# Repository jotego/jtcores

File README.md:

# JTCORES FPGA Arcade Hardware by Jose Tejada (@topapate)

You can show your appreciation through
* [Patreon](https://patreon.com/jotego)
* [Paypal](https://paypal.me/topapate)
* [Github](https://github.com/sponsors/jotego)

Yes, you always wanted to have an arcade board at home. First you couldn't get it because your parents somehow did not understand you. Then you grow up and your wife doesn't understand you either. Don't worry, JT cores are here to the rescue.

I hope you will have as much fun with this project as I had while working on it!

## Wanna play?

You can find the list of supported games in [jtbin/game_list](https://github.com/jotego/jtbin/blob/master/game_list.md). That list is actually an output of the source code of this repository and gets updated every release. There are 1250+ supported titles at the moment ( September 2026 ).

The compiled versions for some FPGA platforms are in [JTBIN](https://github.com/jotego/jtbin). Most cores are released early for [patrons](https://patreon.com/jotego) so check it out too. [JTFRAME](modules/jtframe/README.md) supports more FPGA platforms than the ones publised in JTBIN. You are welcome to compile the cores for the other platforms. Distribution of the core binary files together with copyrighted ROM files is not permitted.

# Compilation - JTFRAME

Refer to [JTFRAME](modules/jtframe/README.md) for compilation instructions and general information about how the cores are organized.

## Private Support Files

Set the `JOTEGO` environment variable to the directory used for private JTCORES support files, including core-regression and scene-regression data used by privately run GitHub Actions. Scene data is stored below `$JOTEGO/scenes/<core-name>/<set-name>`.

When `jtsim -s <scene>` is run from a core verification folder such as `cores/rastan/ver/rbisland`, it requires `JOTEGO` and creates `scenes` as a symbolic link to `$JOTEGO/scenes/rastan/rbisland`. Define `JOTEGO` before running scene simulations.

Master branch health:

# Schematics

Some core have KiCAD schematics for the arcade PCB. This is part of the core research effort and it is important on its own. The schematics folders are called *sch* and can be found in some core folders.

All schematics use the same set of symbol components from [JTKICAD](modules/jtkicad/README.md)

## Troubleshooting

* If you have in-game problems, please read the text file specific to that core. Sometimes it's just that the games has more buttons than you think
* Continue the game: some early arcade games require you to hold the fire button while pressing 1P to continue

## Keyboard

For MiST and MiSTer: games can be controlled with both game pads and keyboard. The keyboard follows the same layout as MAME's default.

    F2      Service mode
    F3      Game reset
    T       Tilt
    P       Pause (in some games, you can disable the credits screen by pressing 1P)
    1,2,3,4 1P..4O start buttons
    5,6     Left and right coin inputs
    9       Service

    cursors 1P direction
    CTRL    1P button 1
    ALT     1P button 2
    space   1P button 3

    R,F,G,D 2P direction
    Q,S,A   2P buttons 3,2 and 1

# Credits

Jose Tejada Gomez. Twitter @topapate
The project is hosted in http://www.github.com/jotego/jtcores
License: GPL3, you are obligued to publish your code if you use mine

Thank you all!
```
+--------------------------------------------------------------------------------+
|oooooooooooooooooooooooooooooooooo+++++++++++ooooooooooooooooooooooooooooooooooo|
|ooooooooooooooooooooooooooooooooo+. .    . .+ooooooooooooooooooooooooooooooooooo|
|ooooooooooooooooooooooooooooooooo~         :o++ooooooooooooooooooooooooooooooooo|
|oooooooooooooooooooooooooooo+ooo+.        .++.:oo+oo+oooooo+o+oo+oooooo++ooooooo|
|ooooooooooooooooooooooooo+.......          .. .............................:oooo|
|oooooooooooooooooooooooo+.                                                .+o+oo|
|oooooooooooooooooooooooo:                                                 :o:.+o|
|ooooooooooooooooooooooo+.                                                .++.:oo|
|ooooooooooooooooooooooo:.....           ...........          ....... ....:o~.+oo|
|oooooooooooooooooooooooo+++++~         ~+++:++:++++.         ++++++++++++++.+ooo|
|oooooooooooooooooooooooooo+:~         .++.~:::::::.         .o+.~:::::::::::+ooo|
|oooooooooooooooooooooooooooo:         :o~.+oooooo+.         ++.~oooooooooooooooo|
|ooo~........~oooooooooooooo+.        .++.:ooooooo+         ~o:.+oooooooooooooooo|
|oo:         ~o++ooooooooooo.         +o~.ooooooo+.        .++.~ooooooooooooooooo|
|oo.         :+.:ooooooooo+.         ~o+.+ooooooo:         ~o:.+ooooooooooooooooo|
|oo.         ...~:::::::..          .++.~ooooooo+.        .o+.:oooooooooooooooooo|
|oo~                               ~o+..+ooooooo~         +o~.+oooooooooooooooooo|
|oo+.                           .~+o+..+ooooooo+.        .o+.+ooooooooooooooooooo|
|oooo~.                       .:+o+..:+oooooooo.         +o..oooooooooooooooooooo|
|ooooo+:...              ..~:+++:..:+ooooooooo+         .o+.+oooooooooooooooooooo|
|ooooooo+++::::::::::++++++++~~.~++ooooooooooo+:+:::::+:++.~ooooooooooooooooooooo|
|ooooooooo+++:::::::::~:~~~~:++oooooooooooooooooo+::::~::~.+ooooooooooooooooooooo|
|oooooooooooooo+o+oo++++o+ooooooooooooooooooooooo+o+++o++o+oooooooooooooooooooooo|
+--------------------------------------------------------------------------------+
```

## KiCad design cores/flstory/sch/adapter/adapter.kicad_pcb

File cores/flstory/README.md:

# JTFLSTORY, FPGA hardware compatible with Taito's FairyLand Story software

This work is based on the schematic work we did on an original FairyLand arcade
PCB. The board turned out to be full of surprises.

# Differences with Emulation (as of Dec. 2025)

The following features are present on the hardware and seem to be missing on
emulators:

- sprite count limited to 8 per line without blinking, more than 8 sprites can be shown but some will blink
- there is a RAM that sets the scroll-sprite priority, not fixed values
- background tile flip control bits can be ignored by means of a global control bit
- some MCU features are missing, such CPU bus sharing via bus request/acknowledgement
- there are a lot of analog audio features that the sound CPU can control, such as balance, trebble, bass...
  the balance feature of amplifier TA7630 is used to alter the relative volume of the two MSM5232 audio channels, so it plays an important role in how the melody sounds
- there are two palette banks (not one)
- there are two background tile banks (not one)
- the priority bits for sprites and scroll tiles are three and two (fewer used in emulation)
- there is support for a light gun on the board

## PSX GunCon on MiSTer

Light-gun games can use an NTSC PlayStation GunCon through a MiSTer PSX SNAC
adapter. In the OSD select **User port -> PSX GunCon SNAC**. This takes over
the physical User Port, so DB15 joystick and UART modes cannot be used at the
same time; USB/Bluetooth gamepads and keyboard controls still work. Trigger is
action button 1, B/Cross is action button 2, A/Start is Start, and Select is
Coin.

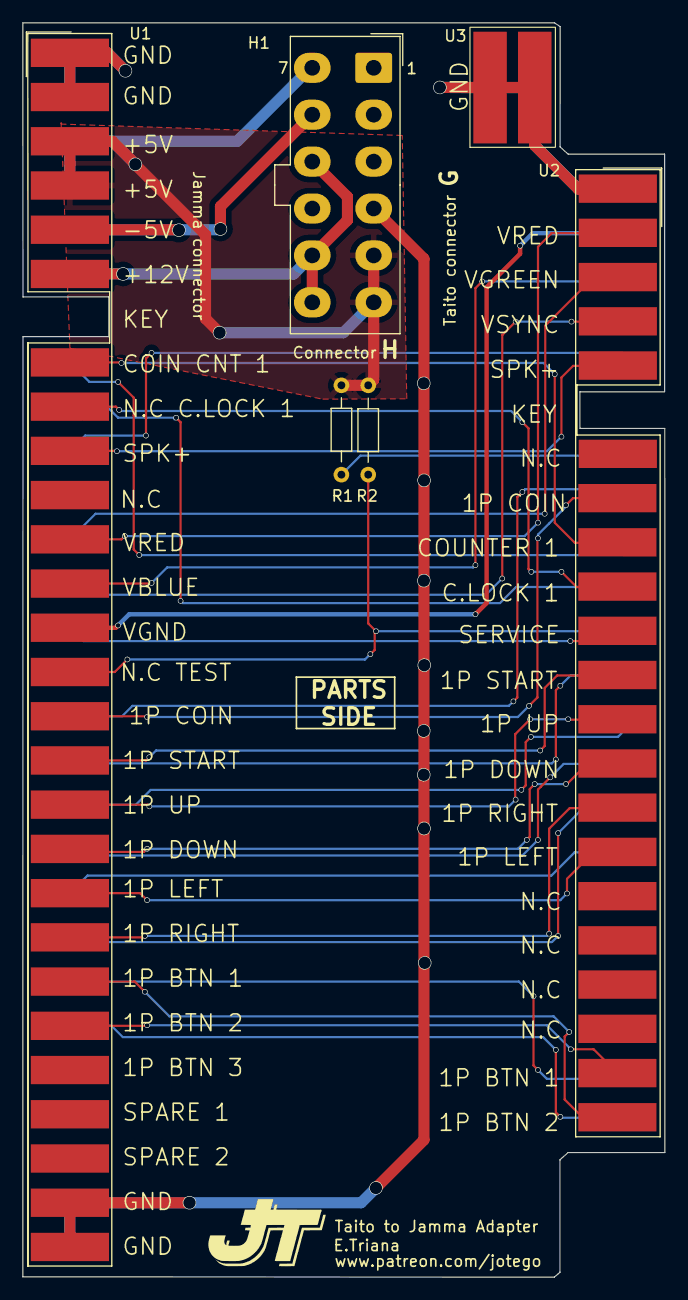
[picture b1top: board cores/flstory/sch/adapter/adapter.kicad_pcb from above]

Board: 2 copper layers, 57.5 x 112.3 mm, 6 parts (0 on the bottom side), 34 nets.

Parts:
H1: Conn_02x06_TB; Molex_Mini-Fit_Jr_5566-12A_2x06_P4.20mm_Vertical
R1, R2: 100kΩ; Resistor P_8mm
U1: JAMMA_MALE; JAMMA MALE
U2: Taito conn_G_adapter_ps; TAITO CONN FOR ADAPTER
U3: Test_point; Test point 3mmx10mm

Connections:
+12V: H1.9, H1.11, H1.12, U1.6 (+12V), U1.F (+12V)
-5V: H1.8, U1.5 (-5V), U1.E (-5V)
/1P_BTN_1: U1.23 (1P_BTN_2), U2.21 (1P_BTN_1)
/1P_BTN_2: U1.22 (1P_BTN_1), U2.22 (1P_BTN_2)
/1P_DOWN: U1.19 (1P_DOWN), U2.14 (1P_DOWN)
/1P_LEFT: U1.20 (1P_LEFT), U2.16 (1P_LEFT)
/1P_RIGHT: U1.21 (1P_RIGHT), U2.15 (1P_RIGHT)
/1P_START: U1.17 (1P_START), U2.12 (1P_START)
/1P_UP: U1.18 (1P_UP), U2.13 (1P_UP)
/C.LOCK_1: U1.9 (NC_C.LOCK_1), U2.10 (C.LOCK_1)
/COIN_1: U1.16 (COIN_1), U2.8 (COIN_1)
/COUNTER_1: U1.8 (COIN_CNT_1), U2.9 (COUNTER_1)
/SERVICE: U1.R (SERVICE), U2.11 (SERVICE)
/SPEAKER(+): U1.10 (SPEAKER_(+)), U2.5 (SPEACKER(+))
/TILT: R2.1, U1.15 (TILT), U2.M (TILT)
/VBLUE: U1.13 (VBLUE), U2.C (VBLUE)
/VGND: U1.14 (VIDEO_GND), U2.B (VIDEO_GND)
/VGREEN: U1.N (VGREEN), U2.3 (VGREEN)
/VRED: U1.12 (VRED), U2.2 (VRED)
/VSYNC: U1.P (VSYNC), U2.4 (VSYNC)
GND: H1.1, H1.2, H1.3, H1.4, U1.1 (GND), U1.2 (GND), U1.27 (GND), U1.28 (GND), U1.A (GND), U1.B (GND), U1.e (GND), U1.f (GND), U2.1 (GND), U2.A (GND), U3.1, U3.2, U3.3, U3.4
unnamed: U1.Z (2P_BTN_1), U2.Y (2P_BTN_1)
unnamed: U1.a (2P_BTN_2), U2.Z (2P_BTN_2)
unnamed: U1.W (2P_DOWN), U2.R (2P_DOWN)
unnamed: U1.X (2P_LEFT), U2.T (2P_LEFT)
unnamed: U1.Y (2P_RIGHT), U2.S (2P_RIGHT)
unnamed: U1.U (2P_START), U2.N (2P_START)
unnamed: U1.V (2P_UP), U2.P (2P_UP)
unnamed: U1.T (COIN_2), U2.J (COIN_2)
unnamed: U1.J (COIN_CNT_2), U2.K (COUNTER_2)
unnamed: U1.K (NC_C.LOCK_2), U2.L (C.LOCK_2)
unnamed: U1.L (SPEAKER_(-)), U2.E (SPEAKER(-))
unnamed: R1.2, U2.H (RESET)
VCC: H1.5, H1.6, H1.7, R1.1, R2.2, U1.3 (+5V), U1.4 (+5V), U1.C (+5V), U1.D (+5V)

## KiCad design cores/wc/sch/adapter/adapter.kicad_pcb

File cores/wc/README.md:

# Grid Iron

# Test Mode

- Hold 1P and 2P while resetting the machine to enter test mode
- Hold shot button to keep the grid on display. Press again to continue

# Simulation Notes

| Simulation              | Command                   |
|:------------------------|:--------------------------|
| Grid image              | `jtsim -w 270 -video 296` |
| Start of subsidiary CPU | `jtsim -w -video 30`      |

# PCB Notes

The schematic extraction was done from a bootleg board, but it was carefully compared with an original one. These are the differences:

- original PCB has through-hole vias whereas the bootleg has filled vias
- original uses three custom packages from Mitsubishi with logic inside. These were replaced by a small daughter board on the bootleg, serving the same functionality
- different edge connectors
- debug edge connector on video board not present on bootleg
- cabinet input logic partly missing and rewired on the bootleg to replace the trackball interface for a joystick one
- different power amplifier for sound without heat sink on the bootleg
- slightly different frequencies for crystal oscillators (cost reduction?)
- device reference markers (silkscreen) on bootleg have reversed order on bootleg

Note that the schematic passes KiCAD electrical rule check with zero errors.

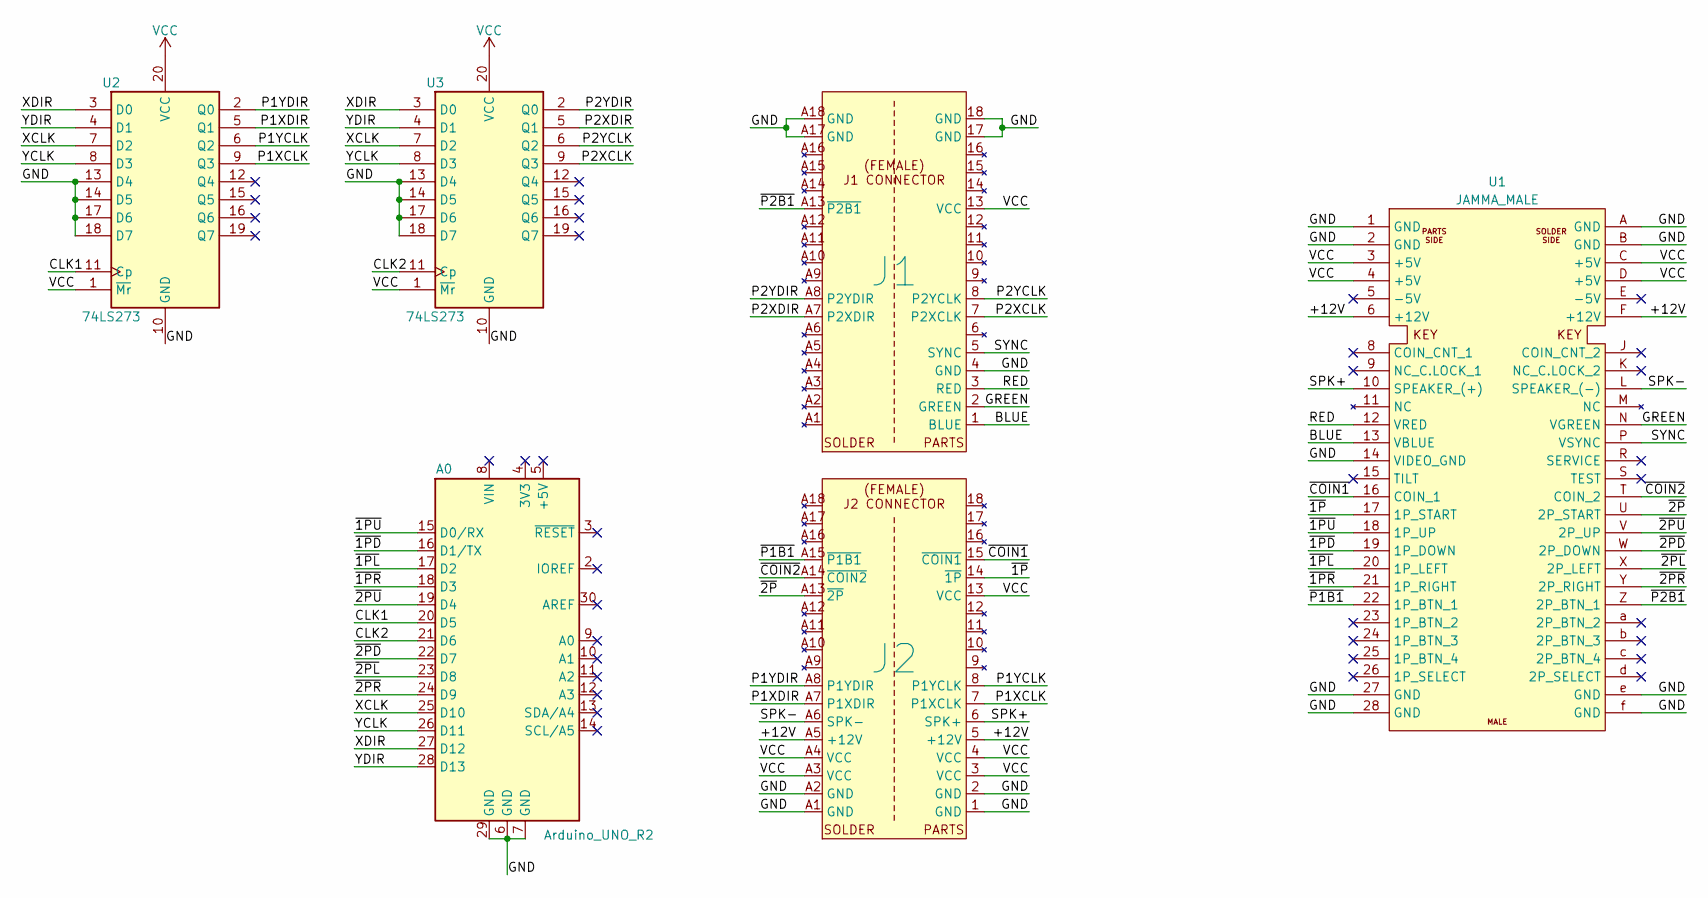
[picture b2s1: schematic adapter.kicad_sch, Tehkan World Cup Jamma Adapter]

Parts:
A0: Arduino_UNO_R2
J1, J2: thekan_wc
U1: JAMMA_MALE; JAMMA MALE
U2, U3: 74LS273; DIP-20_W7.62mm_Socket

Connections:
/+12V: J2.5 (+12V), J2.A5 (+12V), U1.6 (+12V), U1.F (+12V)
/BLUE: J1.1 (BLUE), U1.13 (VBLUE)
/CLK1: A0.20 (D5), U2.11 (Cp)
/CLK2: A0.21 (D6), U3.11 (Cp)
/GND: A0.6 (GND), A0.7 (GND), A0.29 (GND), J1.4 (GND), J1.17 (GND), J1.18 (GND), J1.A17 (GND), J1.A18 (GND), J2.1 (GND), J2.2 (GND), J2.A1 (GND), J2.A2 (GND), U1.1 (GND), U1.2 (GND), U1.14 (VIDEO_GND), U1.27 (GND), U1.28 (GND), U1.A (GND), U1.B (GND), U1.e (GND), U1.f (GND), U2.10 (GND), U2.13 (D4), U2.14 (D5), U2.17 (D6), U2.18 (D7), U3.10 (GND), U3.13 (D4), U3.14 (D5), U3.17 (D6), U3.18 (D7)
/GREEN: J1.2 (GREEN), U1.N (VGREEN)
/P1XCLK: J2.7 (P1XCLK), U2.9 (Q3)
/P1XDIR: J2.A7 (P1XDIR), U2.5 (Q1)
/P1YCLK: J2.8 (P1YCLK), U2.6 (Q2)
/P1YDIR: J2.A8 (P1YDIR), U2.2 (Q0)
/P2XCLK: J1.7 (P2XCLK), U3.9 (Q3)
/P2XDIR: J1.A7 (P2XDIR), U3.5 (Q1)
/P2YCLK: J1.8 (P2YCLK), U3.6 (Q2)
/P2YDIR: J1.A8 (P2YDIR), U3.2 (Q0)
/RED: J1.3 (RED), U1.12 (VRED)
/SPK+: J2.6 (SPK+), U1.10 (SPEAKER_(+))
/SPK-: J2.A6 (SPK-), U1.L (SPEAKER_(-))
/SYNC: J1.5 (SYNC), U1.P (VSYNC)
/XCLK: A0.25 (D10), U2.7 (D2), U3.7 (D2)
/XDIR: A0.27 (D12), U2.3 (D0), U3.3 (D0)
/YCLK: A0.26 (D11), U2.8 (D3), U3.8 (D3)
/YDIR: A0.28 (D13), U2.4 (D1), U3.4 (D1)
/~1PD: A0.16 (D1/TX), U1.19 (1P_DOWN)
/~1PL: A0.17 (D2), U1.20 (1P_LEFT)
/~1PR: A0.18 (D3), U1.21 (1P_RIGHT)
/~1PU: A0.15 (D0/RX), U1.18 (1P_UP)
/~1P: J2.14 (~1P), U1.17 (1P_START)
/~2PD: A0.22 (D7), U1.W (2P_DOWN)
/~2PL: A0.23 (D8), U1.X (2P_LEFT)
/~2PR: A0.24 (D9), U1.Y (2P_RIGHT)
/~2PU: A0.19 (D4), U1.V (2P_UP)
/~2P: J2.A13 (~2P), U1.U (2P_START)
/~COIN1: J2.15 (~COIN1), U1.16 (COIN_1)
/~COIN2: J2.A14 (~COIN2), U1.T (COIN_2)
/~P1B1: J2.A15 (~P1B1), U1.22 (1P_BTN_1)
/~P2B1: J1.A13 (~P2B1), U1.Z (2P_BTN_1)
VCC: J1.13 (VCC), J2.3 (VCC), J2.4 (VCC), J2.13 (VCC), J2.A3 (VCC), J2.A4 (VCC), U1.3 (+5V), U1.4 (+5V), U1.C (+5V), U1.D (+5V), U2.1 (~Mr), U2.20 (VCC), U3.1 (~Mr), U3.20 (VCC)

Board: 2 copper layers, 6 parts (0 on the bottom side), 37 nets, no tracks yet.
